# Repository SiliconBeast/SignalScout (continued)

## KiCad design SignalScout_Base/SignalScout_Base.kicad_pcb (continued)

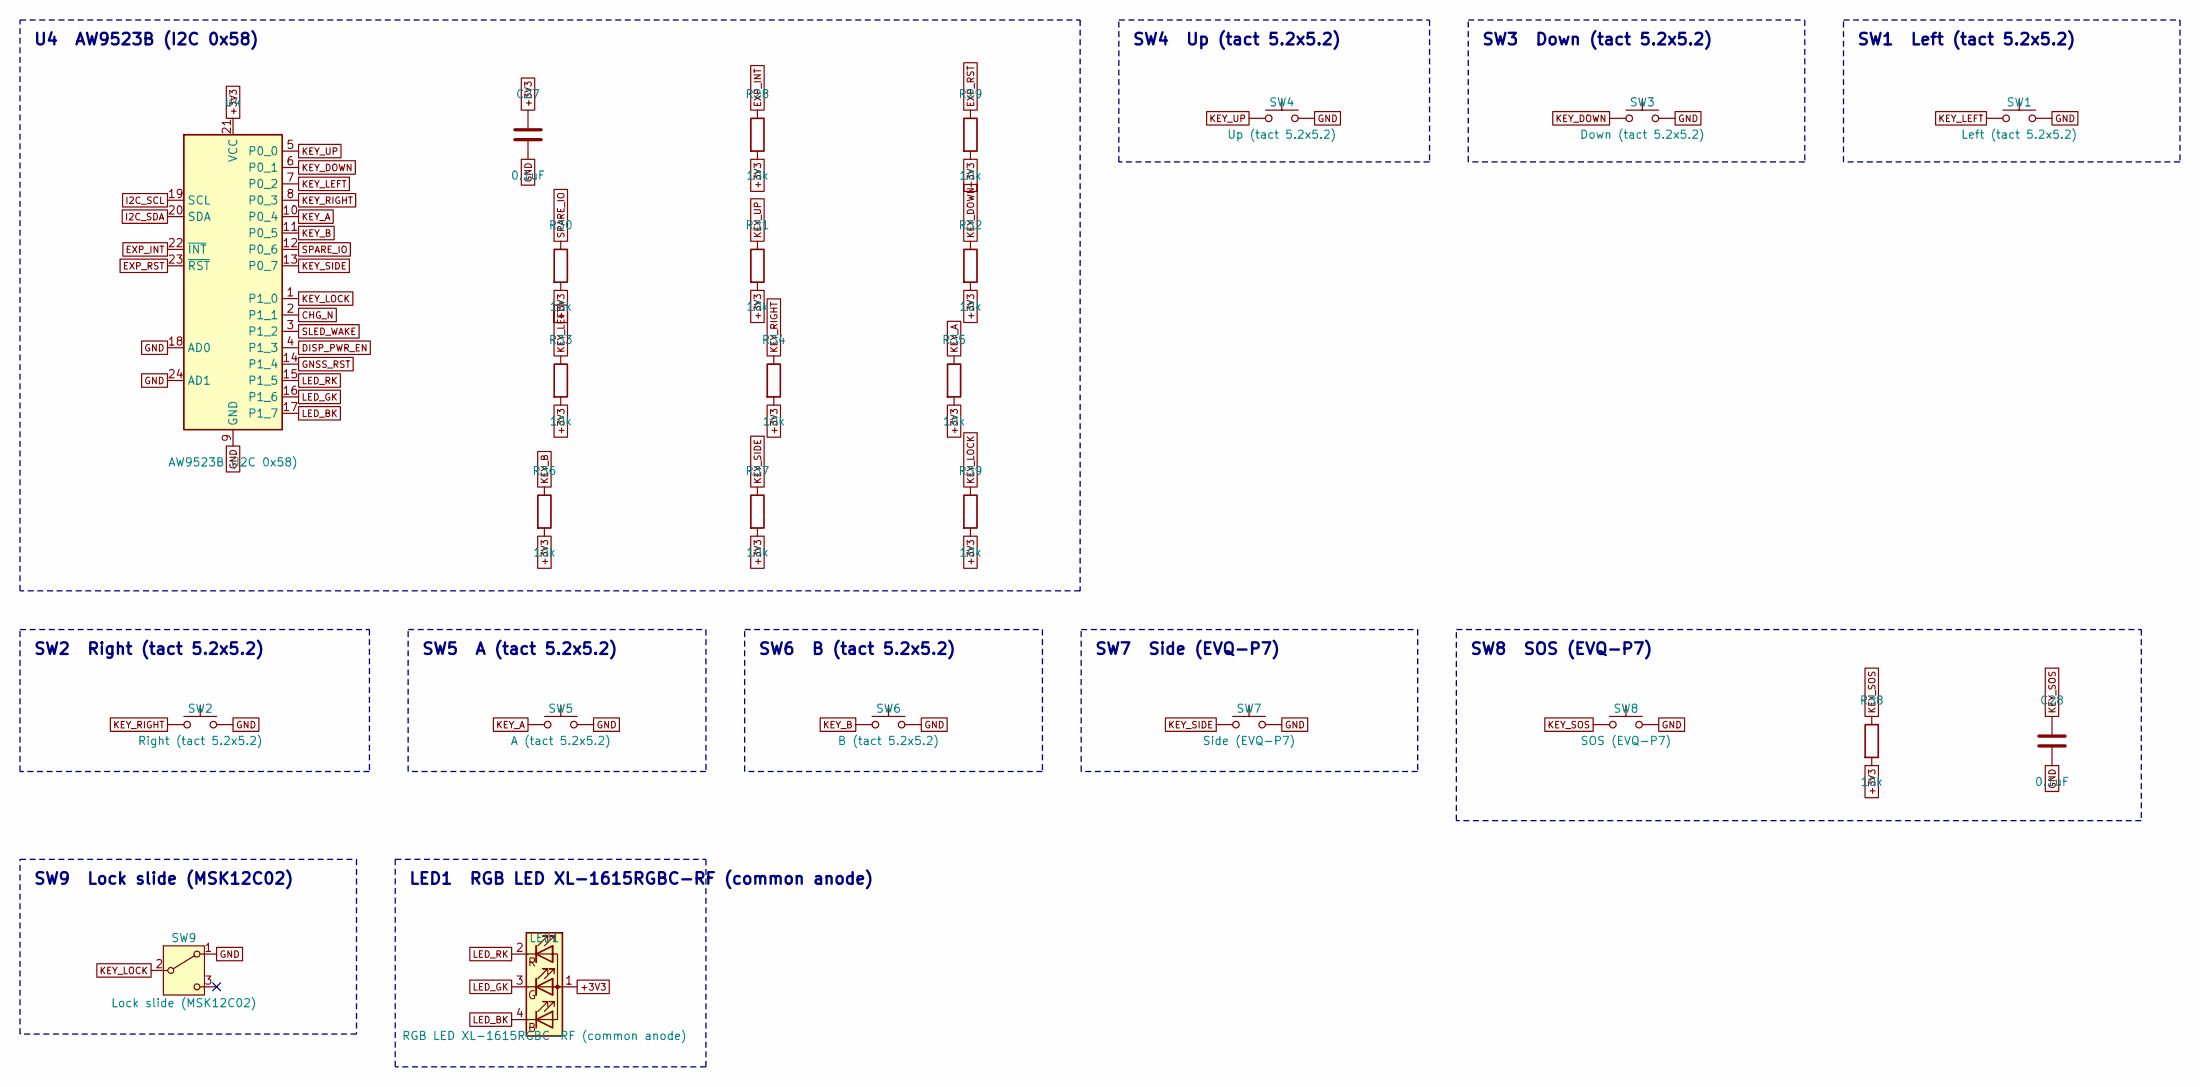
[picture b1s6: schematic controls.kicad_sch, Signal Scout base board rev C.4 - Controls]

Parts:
C27, C28: 0.1uF; C_0402_1005Metric
LED1: RGB LED XL-1615RGBC-RF (common anode); LED_RGB_XL-1615RGBC-RF
R28, R29, R30, R31, R32, R33, R34, R35, R36, R37, R38, R39: 10k; R_0402_1005Metric
SW1: Left (tact 5.2x5.2); SW_SPST_TL3342
SW2: Right (tact 5.2x5.2); SW_SPST_TL3342
SW3: Down (tact 5.2x5.2); SW_SPST_TL3342
SW4: Up (tact 5.2x5.2); SW_SPST_TL3342
SW5: A (tact 5.2x5.2); SW_SPST_TL3342
SW6: B (tact 5.2x5.2); SW_SPST_TL3342
SW7: Side (EVQ-P7); SW_SPST_EVQP7A
SW8: SOS (EVQ-P7); SW_SPST_EVQP7A
SW9: Lock slide (MSK12C02); SW_SPDT_PCM12
U4: AW9523B (I2C 0x58); QFN-24-1EP_4x4mm_P0.5mm_EP2.7x2.7mm

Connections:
+3V3: C27.1, LED1.1 (A), R28.2, R29.2, R30.2, R31.2, R32.2, R33.2, R34.2, R35.2, R36.2, R37.2, R38.2, R39.2, U4.21 (VCC); also elsewhere on the board
CHG_N: U4.2 (P1_1); also elsewhere on the board
DISP_PWR_EN: U4.4 (P1_3); also elsewhere on the board
EXP_INT: R28.1, U4.22 (~INT); also elsewhere on the board
EXP_RST: R29.1, U4.23 (~RST)
GND: C27.2, C28.2, SW1.2, SW2.2, SW3.2, SW4.2, SW5.2, SW6.2, SW7.2, SW8.2, SW9.1 (A), U4.9 (GND), U4.18 (AD0), U4.24 (AD1), U4.25 (GND); also elsewhere on the board
GNSS_RST: U4.14 (P1_4); also elsewhere on the board
I2C_SCL: U4.19 (SCL); also elsewhere on the board
I2C_SDA: U4.20 (SDA); also elsewhere on the board
KEY_A: R35.1, SW5.1, U4.10 (P0_4)
KEY_B: R36.1, SW6.1, U4.11 (P0_5)
KEY_DOWN: R32.1, SW3.1, U4.6 (P0_1)
KEY_LEFT: R33.1, SW1.1, U4.7 (P0_2)
KEY_LOCK: R39.1, SW9.2 (B), U4.1 (P1_0)
KEY_RIGHT: R34.1, SW2.1, U4.8 (P0_3)
KEY_SIDE: R37.1, SW7.1, U4.13 (P0_7)
KEY_SOS: C28.1, R38.1, SW8.1; also elsewhere on the board
KEY_UP: R31.1, SW4.1, U4.5 (P0_0)
SLED_WAKE: U4.3 (P1_2); also elsewhere on the board
SPARE_IO: R30.1, U4.12 (P0_6); also elsewhere on the board

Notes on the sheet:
U4 AW9523B (I2C 0x58)
SW4 Up (tact 5.2x5.2)
SW3 Down (tact 5.2x5.2)
SW1 Left (tact 5.2x5.2)
SW2 Right (tact 5.2x5.2)
SW5 A (tact 5.2x5.2)
SW6 B (tact 5.2x5.2)
SW7 Side (EVQ-P7)
SW8 SOS (EVQ-P7)
SW9 Lock slide (MSK12C02)
LED1 RGB LED XL-1615RGBC-RF (common anode)

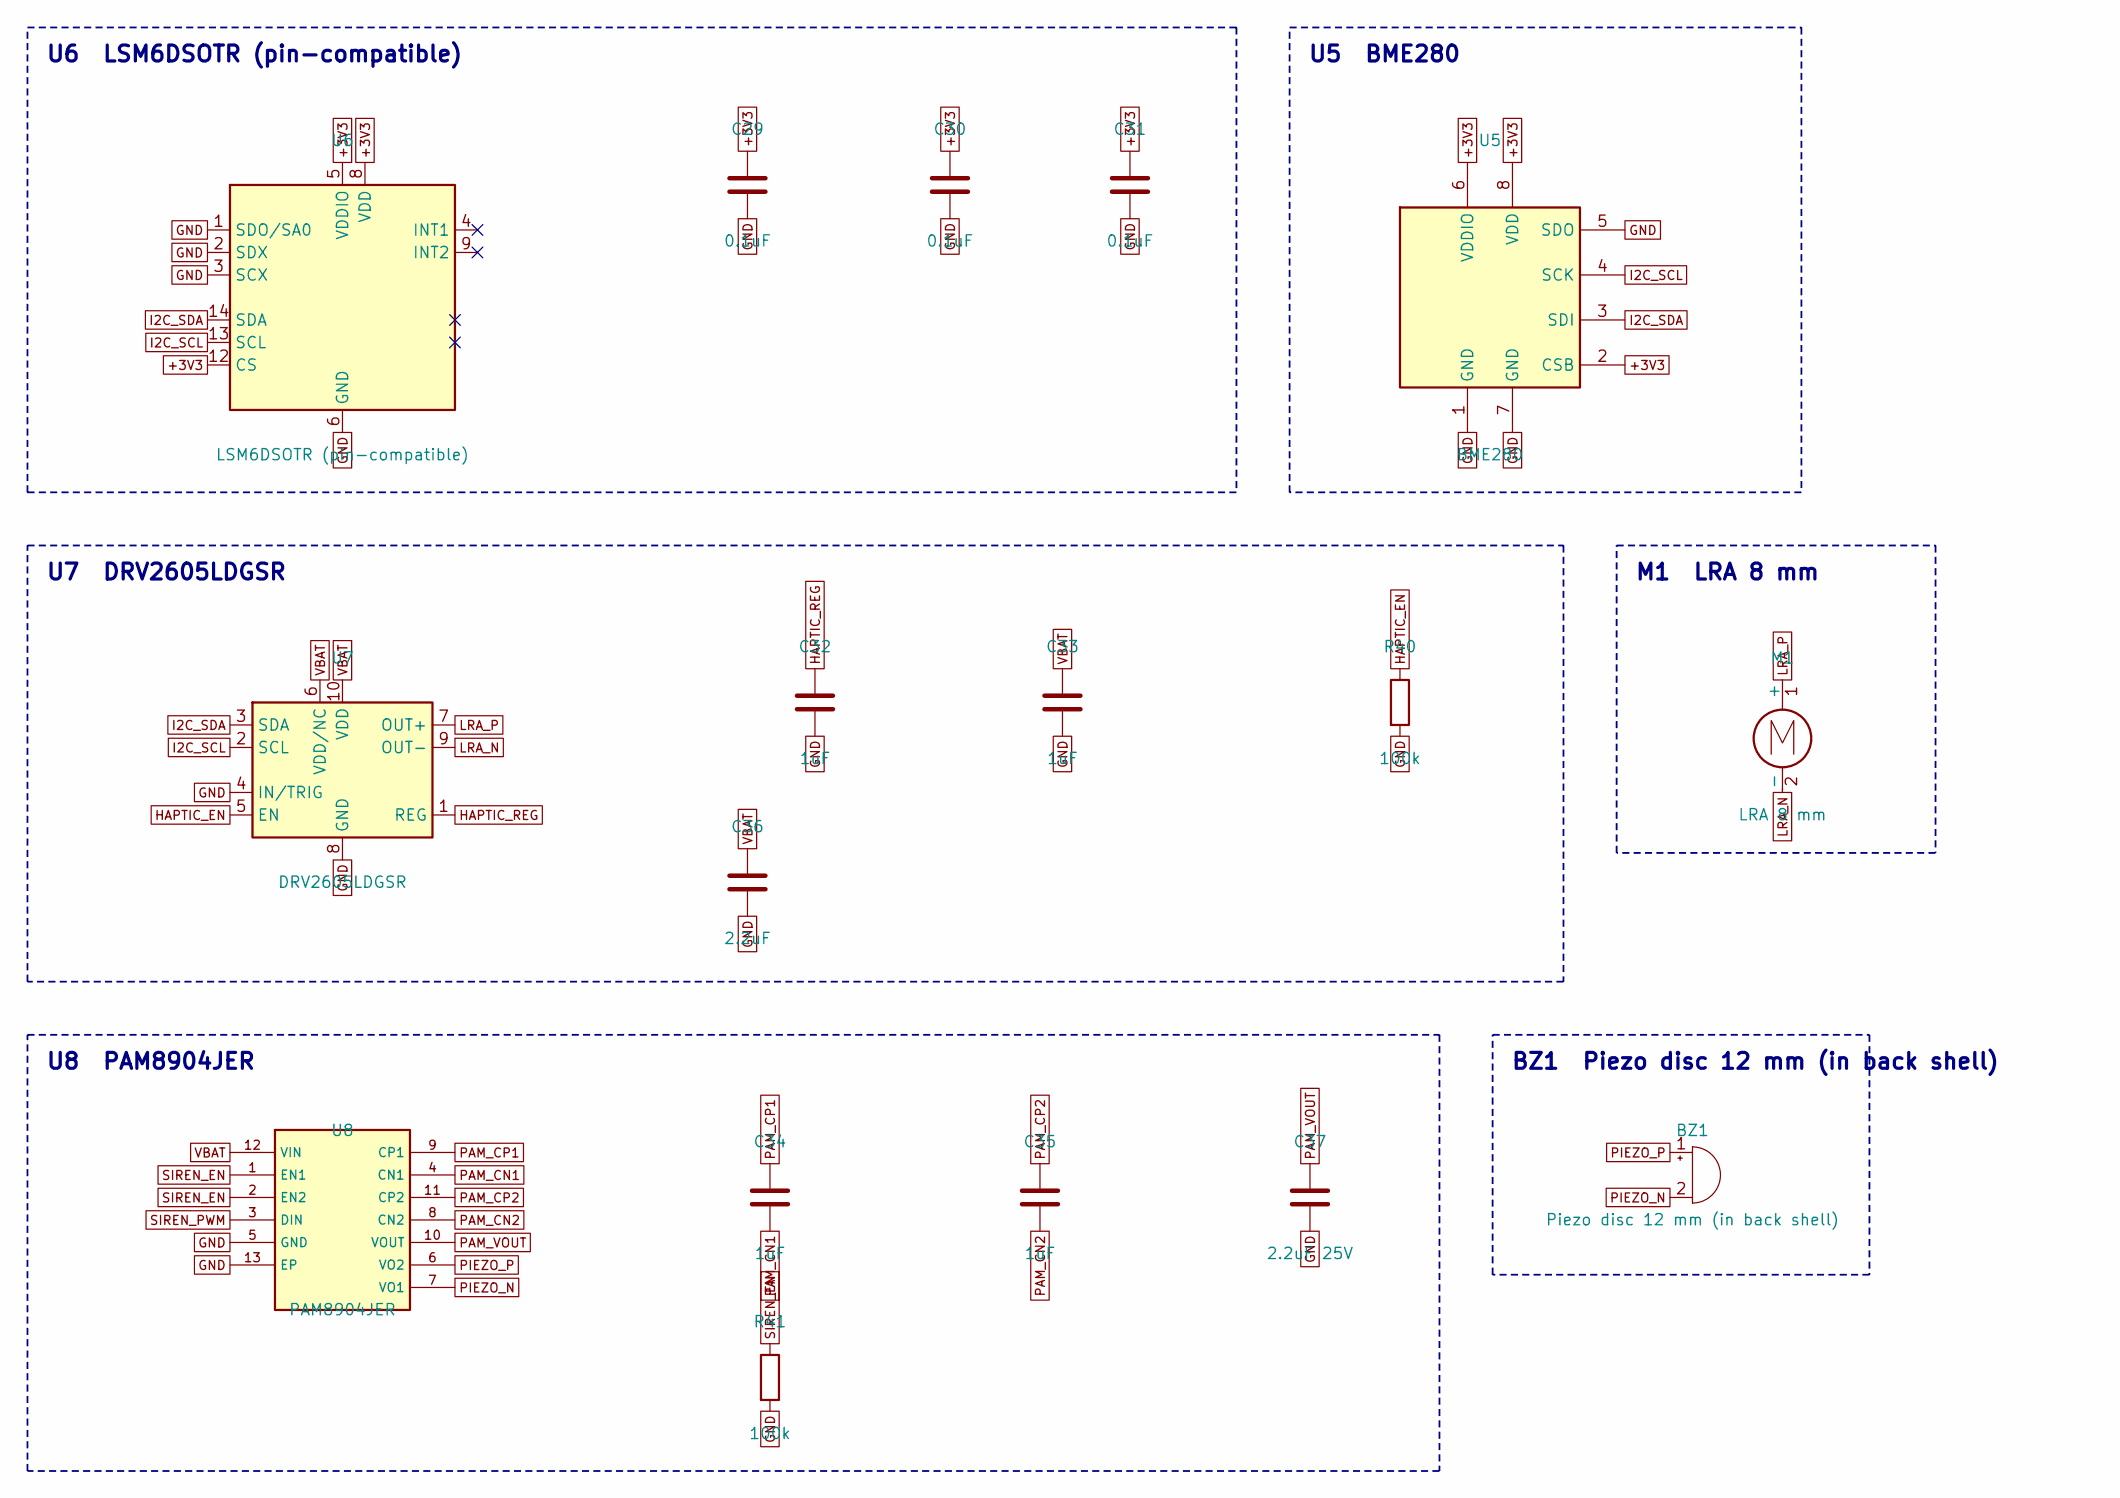
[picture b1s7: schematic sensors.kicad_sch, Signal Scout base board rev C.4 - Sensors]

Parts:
BZ1: Piezo disc 12 mm (in back shell); WirePads_1x02_P2.6mm_SMD
C29, C30, C31: 0.1uF; C_0402_1005Metric
C32, C33, C34, C35: 1uF; C_0402_1005Metric
C36: 2.2uF; C_0603_1608Metric
C37: 2.2uF 25V; C_0603_1608Metric
M1: LRA 8 mm; LRA_D8_WireLeads
R40, R41: 100k; R_0402_1005Metric
U5: BME280; Bosch_LGA-8_2.5x2.5mm_P0.65mm_ClockwisePinNumbering
U6: LSM6DSOTR (pin-compatible); LGA-14_3x2.5mm_P0.5mm_LayoutBorder3x4y
U7: DRV2605LDGSR; VSSOP-10_3x3mm_P0.5mm
U8: PAM8904JER; QFN-12-1EP_3x3mm_P0.5mm_EP1.6x1.6mm

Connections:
+3V3: C29.1, C30.1, C31.1, U5.2 (CSB), U5.6 (VDDIO), U5.8 (VDD), U6.5 (VDDIO), U6.8 (VDD), U6.12 (CS); also elsewhere on the board
GND: C29.2, C30.2, C31.2, C32.2, C33.2, C36.2, C37.2, R40.2, R41.2, U5.1 (GND), U5.5 (SDO), U5.7 (GND), U6.1 (SDO/SA0), U6.2 (SDX), U6.3 (SCX), U6.6 (GND), U6.7 (GND), U7.4 (IN/TRIG), U7.8 (GND), U8.5 (GND), U8.13 (EP); also elsewhere on the board
HAPTIC_EN: R40.1, U7.5 (EN); also elsewhere on the board
HAPTIC_REG: C32.1, U7.1 (REG)
I2C_SCL: U5.4 (SCK), U6.13 (SCL), U7.2 (SCL); also elsewhere on the board
I2C_SDA: U5.3 (SDI), U6.14 (SDA), U7.3 (SDA); also elsewhere on the board
IMU_INT: U6.9 (INT2); also elsewhere on the board
LRA_N: M1.2 (-), U7.9 (OUT-)
LRA_P: M1.1 (+), U7.7 (OUT+)
PAM_CN1: C34.2, U8.4 (CN1)
PAM_CN2: C35.2, U8.8 (CN2)
PAM_CP1: C34.1, U8.9 (CP1)
PAM_CP2: C35.1, U8.11 (CP2)
PAM_VOUT: C37.1, U8.10 (VOUT)
PIEZO_N: BZ1.2 (-), U8.7 (VO1)
PIEZO_P: BZ1.1 (+), U8.6 (VO2)
SIREN_EN: R41.1, U8.1 (EN1), U8.2 (EN2); also elsewhere on the board
SIREN_PWM: U8.3 (DIN); also elsewhere on the board
VBAT: C33.1, C36.1, U7.6 (VDD/NC), U7.10 (VDD), U8.12 (VIN); also elsewhere on the board

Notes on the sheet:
U6 LSM6DSOTR (pin-compatible)
U5 BME280
U7 DRV2605LDGSR
M1 LRA 8 mm
U8 PAM8904JER
BZ1 Piezo disc 12 mm (in back shell)

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
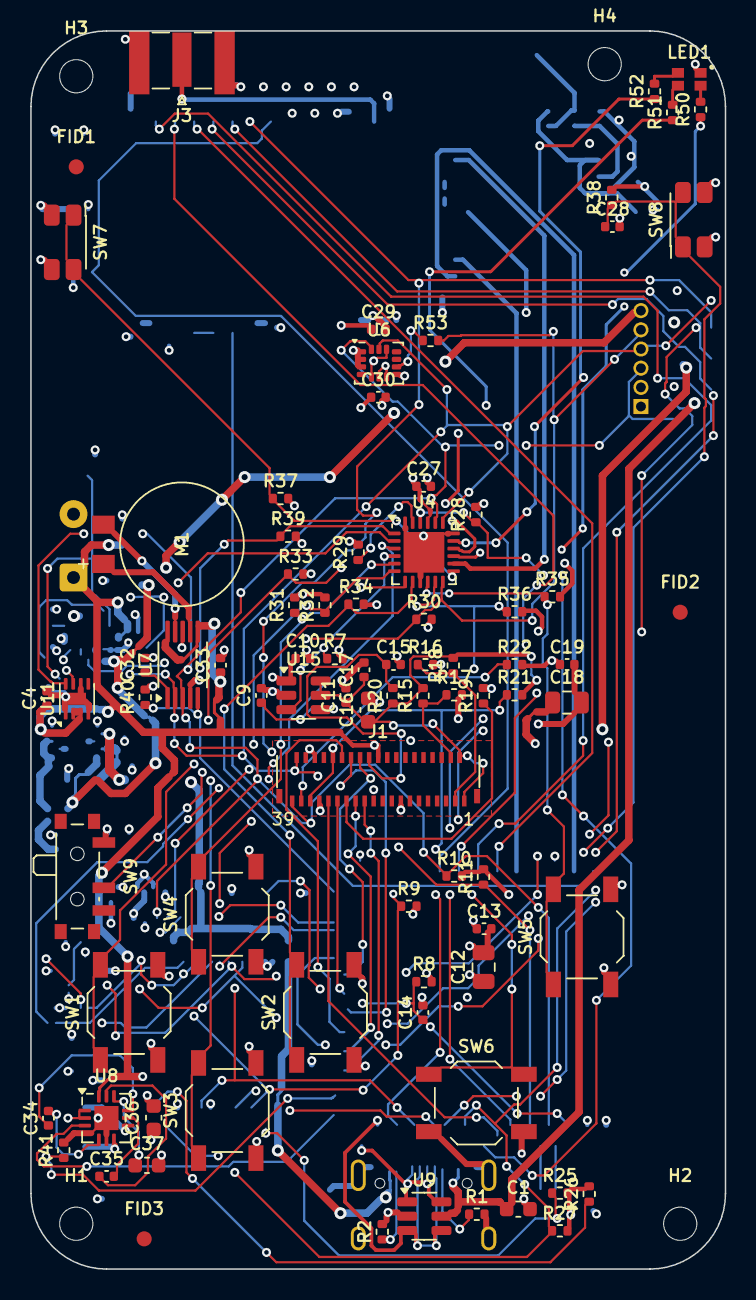
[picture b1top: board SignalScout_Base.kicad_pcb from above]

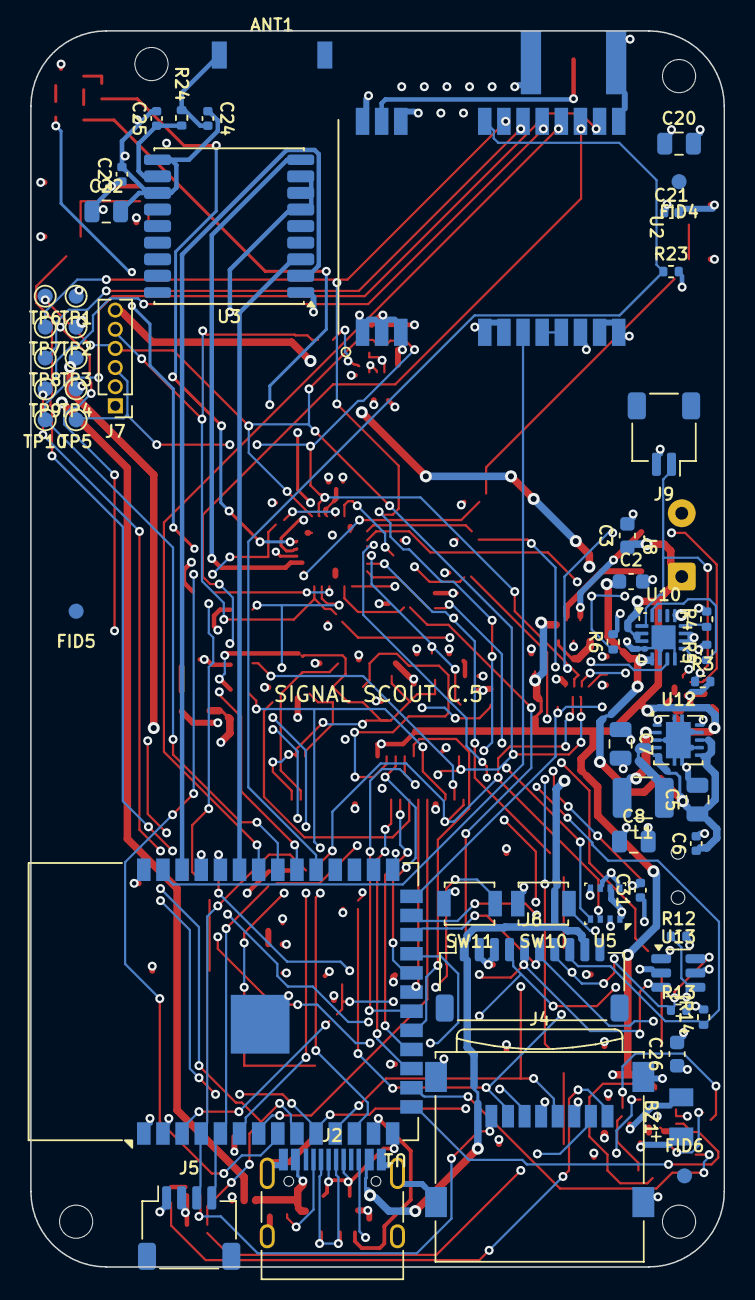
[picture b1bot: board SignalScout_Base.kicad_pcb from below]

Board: 4 copper layers, 46.0 x 82.0 mm, 141 parts (55 on the bottom side), 89 nets.

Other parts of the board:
FID1, FID2, FID3, FID4, FID5, FID6: Fiducial_1mm_Mask2mm
H1, H3: M2; MountingHole_2.2mm_M2
H2, H4: M2 nylon; MountingHole_2.2mm_M2
R50: 82; R_0402_1005Metric
R51, R52: 22; R_0402_1005Metric
R53: 1k; R_0402_1005Metric

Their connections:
IMU_INT: R53.1; also elsewhere on the board
SPARE_IO: R53.2; also elsewhere on the board

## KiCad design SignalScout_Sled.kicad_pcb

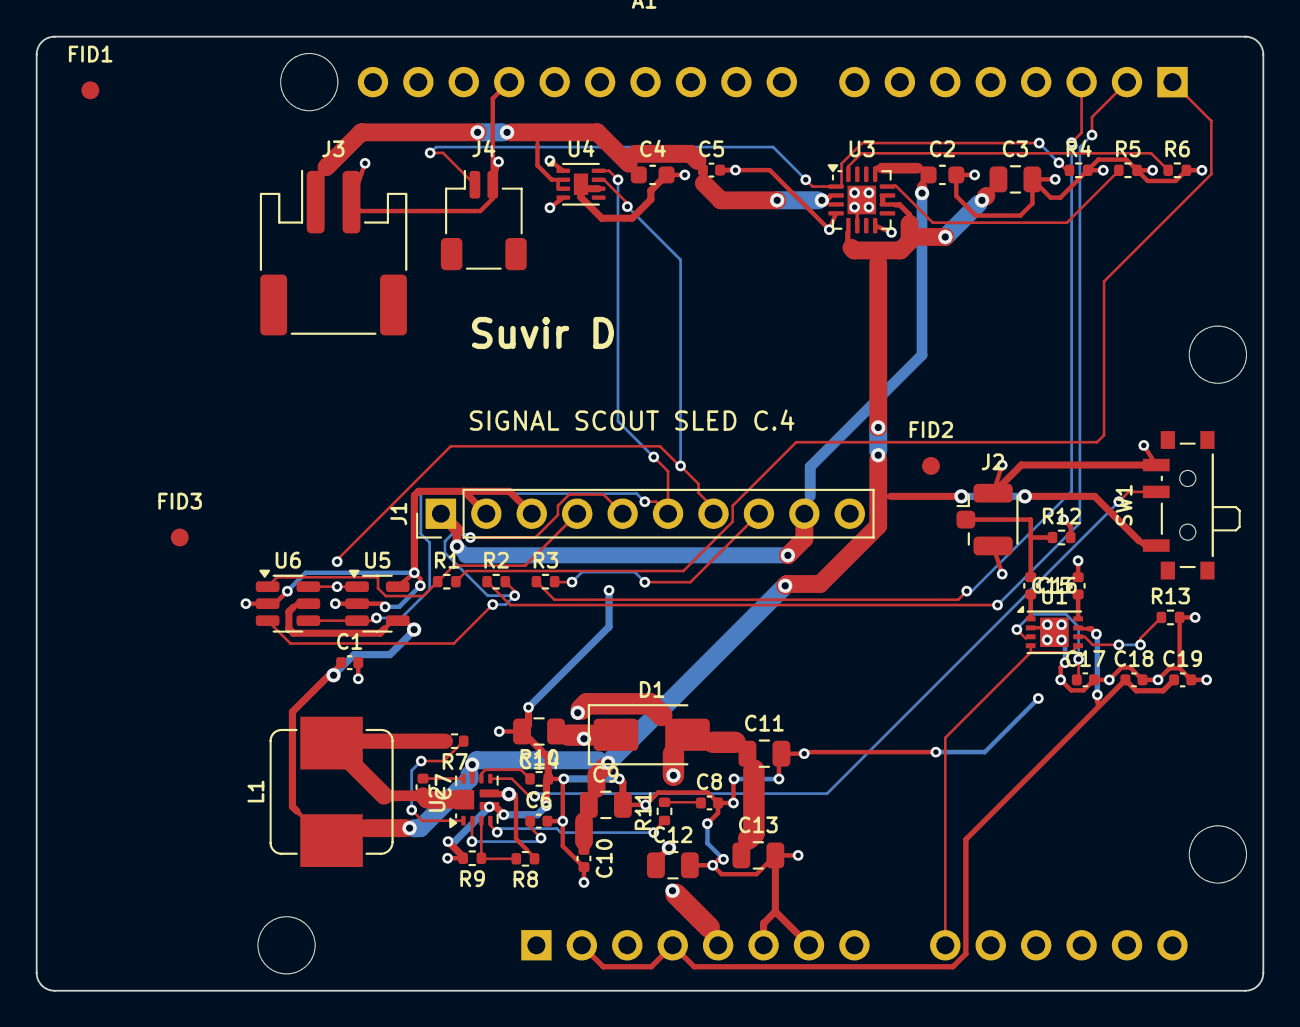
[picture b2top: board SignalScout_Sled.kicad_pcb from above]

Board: 4 copper layers, 68.6 x 53.3 mm, 49 parts (0 on the bottom side), 33 nets.

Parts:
A1: UNO Q headers (ABX00162); UNO_Q_Shield_Headers
C1, C5, C7, C10, C19: 0.1uF; C_0402_1005Metric
C2, C4: 4.7uF; C_0603_1608Metric
C3, C9: 10uF; C_0805_2012Metric
C6: 2.2uF; C_0402_1005Metric
C8: 4.7nF; C_0402_1005Metric
C11, C12, C13, C14: 22uF 10V; C_0805_2012Metric
C15, C16: 47nF; C_0402_1005Metric
C17: 8.2pF; C_0402_1005Metric
C18: 100pF; C_0402_1005Metric
D1: SS54 (5 A, 40 V); D_SMA
FID1, FID2, FID3: Fiducial_1mm_Mask2mm
J1: Pogo pins 2.54 mm (to base); PinHeader_1x10_P2.54mm_Vertical
J2: U.FL to wideband antenna; U.FL_Hirose_U.FL-R-SMT-1_Vertical
J3: LiPo 1S 2000 mAh; JST_PH_S2B-PH-SM4-TB_1x02-1MP_P2.00mm_Horizontal
J4: Battery NTC 10k (103AT) on cell; JST_SH_SM02B-SRSS-TB_1x02-1MP_P1.00mm_Horizontal
L1: 1.5uH 8A (SRP7028A-1R5M); L_Bourns_SRP7028A_7.3x6.6mm
R1, R2, R3: 1k; R_0402_1005Metric
R4: 10k; R_0402_1005Metric
R5: 1.1k; R_0402_1005Metric
R6: 909; R_0402_1005Metric
R7: 301k; R_0402_1005Metric
R8: 340k; R_0402_1005Metric
R9: 100k; R_0402_1005Metric
R10: 169k; R_0402_1005Metric
R11: 17.4k; R_0402_1005Metric
R12: 52.3; R_0402_1005Metric
R13: 8.06k; R_0402_1005Metric
SW1: Sled power (UNO Q on/off); SW_SPDT_PCM12
U1: AD8317ACPZ-R7; LFCSP-8-1EP_3x2mm_P0.5mm_EP1.6x1.65mm
U2: TPS61089RNRR; Texas_VQFN-RNR0011A-11
U3: BQ24074RGTR; VQFN-16-1EP_3x3mm_P0.5mm_EP1.6x1.6mm
U4: MAX17048G+T10; TDFN-8-1EP_2x2mm_P0.5mm_EP0.8x1.2mm
U5: 24AA02E48T-I/OT (sled ID); SOT-23-5
U6: USBLC6-4SC6; SOT-23-6

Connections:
5V_SYS: A1.5, C14.1, D1.1
+5V3_BOOST: C11.1, C12.1, C13.1, D1.2, R8.1, U2.6
AD_CLPF: C17.1, U1.3
AD_TADJ: R13.1, U1.6
AD_VOUT: A1.9, U1.4, U1.5
BOOST_BOOT: C7.1, U2.10
BOOST_CC: C8.1, R11.2
BOOST_COMP: R11.1, U2.4
BOOST_EN: SW1.2, U2.7
BOOST_FB: R8.2, R9.1, U2.3
BOOST_FSW: R7.1, U2.1
BOOST_ILIM: R10.1, U2.8
BOOST_VCC: C6.1, U2.2
GND: A1.6, A1.7, A1.29, C1.2, C2.2, C3.2, C4.2, C5.2, C6.2, C8.2, C9.2, C10.2, C11.2, C12.2, C13.2, C14.2, C16.2, C17.2, C18.2, C19.2, J1.2, J1.3, J2.2, J3.2, J4.2, R4.2, R5.2, R6.2, R9.2, R10.2, R12.2, R13.2, SW1.3, U1.2, U1.9, U2.5, U3.4, U3.6, U3.8, U3.17, U4.1, U4.4, U4.6, U4.9, U5.2, U5.5, U6.2
LX_BOOST: C7.2, L1.2, R7.2, U2.11
RF_IN: C15.1, J2.1, R12.1
RF_INHI: C15.2, U1.1
RF_INLO: C16.1, U1.8
SBAT: C4.1, C5.1, J3.1, U3.2, U3.3, U4.2, U4.3
SLED_RX: J1.5, R2.2, U6.3
SLED_SCL: J1.7, U4.7, U5.1, U6.6
SLED_SDA: J1.6, U4.8, U5.3, U6.4
SLED_TX: J1.4, R1.1, U6.1
SLED_WAKE: J1.8, R3.2
SVSYS: C1.1, C3.1, C9.1, C10.1, L1.1, SW1.1, U2.9, U3.5, U3.10, U3.11, U5.4, U6.5
S_ILIM: R5.1, U3.12
S_ISET: R6.1, U3.16
S_TS: J4.1, R4.1, U3.1
UNOQ_3V3: A1.2, A1.4, C18.1, C19.1, U1.7
UNOQ_RX: A1.15, R1.2
UNOQ_TX: A1.16, R2.1
UNOQ_WAKE: A1.17, R3.1
VBUS: C2.1, J1.1, J1.9, U3.13

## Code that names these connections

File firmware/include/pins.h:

// GENERATED by tools/gen_pins.py from SignalScout_Base.kicad_pcb - do not edit.
#pragma once

// ESP32-S3-WROOM-1 GPIO numbers, named after the schematic nets.
#define PIN_SD_CS           0  // strapping pin: boot mode
#define PIN_LORA_RXEN       1
#define PIN_GNSS_TXD        2
#define PIN_SIREN_PWM       3  // strapping pin: JTAG select
#define PIN_I2C_SDA         4
#define PIN_I2C_SCL         5
#define PIN_TP_INT          6
#define PIN_DISP_TE         7
#define PIN_DISP_RESET      8
#define PIN_LCD_D3          9
#define PIN_LCD_CS         10
#define PIN_LCD_D0         11
#define PIN_LCD_SCK        12
#define PIN_LCD_D1         13
#define PIN_LCD_D2         14
#define PIN_EXP_INT        15
#define PIN_SPI_MISO       16
#define PIN_SPI_MOSI       17
#define PIN_SPI_SCK        18
#define PIN_USB_DN         19
#define PIN_USB_DP         20
#define PIN_KEY_SOS        21
#define PIN_LORA_NSS       38
#define PIN_LORA_BUSY      39
#define PIN_LORA_DIO1      40
#define PIN_LORA_NRST      41
#define PIN_GNSS_RXD       42
#define PIN_SLED_TX        43
#define PIN_SLED_RX        44
#define PIN_HAPTIC_EN      45  // strapping pin: VDD_SPI voltage
#define PIN_SIREN_EN       46  // strapping pin: boot mode / ROM log
#define PIN_SLED_SDA       47
#define PIN_SLED_SCL       48

// AW9523B I/O expander (I2C 0x58). Value = bit index, port 0 = bits 0-7, port 1 = bits 8-15.
#define EXP_KEY_UP             0  // P0_0
#define EXP_KEY_DOWN           1  // P0_1
#define EXP_KEY_LEFT           2  // P0_2
#define EXP_KEY_RIGHT          3  // P0_3
#define EXP_KEY_A              4  // P0_4
#define EXP_KEY_B              5  // P0_5
#define EXP_SPARE_IO           6  // P0_6
#define EXP_KEY_SIDE           7  // P0_7
#define EXP_KEY_LOCK           8  // P1_0
#define EXP_CHG_N              9  // P1_1
#define EXP_SLED_WAKE         10  // P1_2
#define EXP_DISP_PWR_EN       11  // P1_3
#define EXP_GNSS_RST          12  // P1_4
#define EXP_LED_RK            13  // P1_5
#define EXP_LED_GK            14  // P1_6
#define EXP_LED_BK            15  // P1_7

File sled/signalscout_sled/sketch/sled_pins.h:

// GENERATED by tools/gen_pins.py from SignalScout_Sled.kicad_pcb - do not edit.
#pragma once

// Arduino UNO Q header pins, named after the sled schematic nets.
#define PIN_AD_VOUT      A0
#define PIN_UNOQ_RX      D0
#define PIN_UNOQ_TX      D1
#define PIN_UNOQ_WAKE    D2
